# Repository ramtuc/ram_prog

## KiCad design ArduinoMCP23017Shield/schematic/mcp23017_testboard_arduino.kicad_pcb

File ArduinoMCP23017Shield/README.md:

# Arduino MCP23017 Shield

MCP23017 I2C GPIOエキスパンダーを使用したArduino UNO用シールド基板プロジェクトです。I2C通信で16個のGPIOピンを追加し、デジタル入出力を拡張できます。

## 特徴

- **16ピンのGPIO拡張**: MCP23017により16個のデジタルI/Oピンを追加
- **I2C通信**: わずか2本の信号線(SDA/SCL)で制御
- **柔軟な入出力設定**: 各ピンを独立して入力/出力に設定可能
- **アドレス選択可能**: 最大8個のMCP23017を接続可能(アドレス0x20-0x27)
- **2種類のサンプルプログラム**:
  - 出力テスト（シーケンシャルLED点灯）
  - 入出力テスト（入力→出力ループバック）

## ハードウェア

### 回路図

`schematic/` フォルダにKiCadプロジェクトファイルが含まれています：

- `mcp23017_testboard_arduino.kicad_sch` - 回路図
- `mcp23017_testboard_arduino.kicad_pcb` - PCBレイアウト
- `mcp23017_testboard_arduino.pdf` - 回路図PDF
- `bom .xls` - 部品表（BOM）
- `CPL.xlsx` - 部品配置リスト

### MCP23017について

MCP23017は、I2Cインターフェースで制御できる16ビットGPIOエキスパンダーです。

**主な仕様:**
- 16個の双方向I/Oピン（2つの8ビットポート: GPIOA, GPIOB）
- I2C通信（400kHzまで対応）
- 各ピンに内部プルアップ抵抗搭載
- 割り込み機能搭載
- 動作電圧: 1.8V～5.5V

**ピン配置:**
- **GPIOA (PA0-PA7)**: ポートA（ピン0-7）
- **GPIOB (PB0-PB7)**: ポートB（ピン8-15）

### 対応ボード

- Arduino UNO R3
- Arduino UNO R4 Minima
- Arduino UNO R4 WiFi
- ESP32（I2C対応ボード）

## サンプルプログラム

### 1. Arduino_mcp23017_testboard
MCP23017の出力機能テスト - 16ピンをシーケンシャルに点灯

**機能:**
- 16個の出力ピン（PA0-PA7, PB0-PB7）を順番にHIGH/LOW制御
- 各ピンを順次点灯してLEDテストが可能
- 200msごとに次のピンへ移動

**用途:**
- MCP23017の動作確認
- 16個のLED順次点灯
- 出力ポートの配線チェック

**コード例:**
```cpp
#include <Wire.h>
#include <Adafruit_MCP23X17.h>

Adafruit_MCP23X17 mcp;

void setup() {
  Wire.begin();
  mcp.begin_I2C();  // アドレス0x20
  
  // 全16ピンを出力に設定
  for (int i = 0; i < 16; i++) {
    mcp.pinMode(i, OUTPUT);
  }
}

void loop() {
  // 各ピンを順番に点灯
  for (int i = 0; i < 16; i++) {
    mcp.digitalWrite(i, HIGH);
    // 他のピンをLOWに
    for (int j = 0; j < 16; j++) {
      if (j != i) mcp.digitalWrite(j, LOW);
    }
    delay(200);
  }
}
```

### 2. Arduino_mcp23017_testboard_inout
MCP23017の入出力機能テスト - 入力読み取りと出力制御

**機能:**
- **ポートA (PA0-PA7)**: 出力ポート
- **ポートB (PB0-PB7)**: 入力ポート
- ポートBの入力状態をリアルタイムでポートAに反映
- Arduinoのデジタルピン0-7をランダムに制御

**用途:**
- 入力機能の動作確認
- スイッチ入力とLED出力の連動テスト
- ループバックテスト

**コード例:**
```cpp
void setup() {
  Wire.begin();
  mcp.begin_I2C();
  
  // ポートA (PA0-PA7): 出力
  for (int i = 0; i < 8; i++) {
    mcp.pinMode(i, OUTPUT);
  }
  
  // ポートB (PB0-PB7): 入力
  for (int i = 8; i < 16; i++) {
    mcp.pinMode(i, INPUT);
  }
}

void loop() {
  // ポートBの入力をポートAに反映
  for (int i = 0; i < 8; i++) {
    int state = mcp.digitalRead(i + 8);  // PB読み取り
    mcp.digitalWrite(i, state);          // PAに出力
  }
  delay(500);
}
```

## セットアップ

### 1. 必要なライブラリ

Arduino IDEのライブラリマネージャーからインストール：

- **Adafruit MCP23017 Library** (by Adafruit)
- **Wire** (Arduino標準ライブラリ)

```
スケッチ → ライブラリをインクルード → ライブラリを管理
「Adafruit MCP23017」で検索してインストール
```

### 2. ハードウェア接続

**I2C接続:**
- SDA → Arduino A4 (UNO) / GPIO21 (ESP32)
- SCL → Arduino A5 (UNO) / GPIO22 (ESP32)
- VDD → 5V (Arduino) / 3.3V (ESP32)
- GND → GND

**アドレス設定:**
- A0, A1, A2ピンでI2Cアドレスを設定
- デフォルト: 0x20 (A0=A1=A2=GND)

### 3. スケッチのアップロード

```bash
# Arduino IDEでスケッチを開く
Arduino_Schetch/Arduino_mcp23017_testboard/Arduino_mcp23017_testboard.ino
# または
Arduino_Schetch/Arduino_mcp23017_testboard_inout/Arduino_mcp23017_testboard_inout.ino

# ボードを選択: Arduino UNO R3/R4
# ポートを選択
# アップロード
```

## I2Cアドレス設定

MCP23017のI2Cアドレスは、A0、A1、A2ピンで設定します：

| A2 | A1 | A0 | アドレス |
|----|----|----|----------|
| 0  | 0  | 0  | 0x20     |
| 0  | 0  | 1  | 0x21     |
| 0  | 1  | 0  | 0x22     |
| 0  | 1  | 1  | 0x23     |
| 1  | 0  | 0  | 0x24     |
| 1  | 0  | 1  | 0x25     |
| 1  | 1  | 0  | 0x26     |
| 1  | 1  | 1  | 0x27     |

```cpp
// カスタムアドレスで初期化
mcp.begin_I2C(0x21);  // A0=HIGH, A1=A2=LOW
```

## 応用例

### 複数のMCP23017を使用

```cpp
Adafruit_MCP23X17 mcp1;
Adafruit_MCP23X17 mcp2;

void setup() {
  Wire.begin();
  mcp1.begin_I2C(0x20);  // 1つ目
  mcp2.begin_I2C(0x21);  // 2つ目
  
  // 合計32ピンの拡張が可能
}
```

### プルアップ抵抗の有効化

```cpp
// 内部プルアップを有効化（スイッチ入力に便利）
mcp.pinMode(0, INPUT_PULLUP);
```

### 割り込み機能の使用

```cpp
// ピン変化時に割り込みを発生
mcp.setupInterruptPin(0, CHANGE);
```

## トラブルシューティング

### I2Cデバイスが見つからない

1. 配線を確認（SDA/SCL、電源、GND）
2. I2Cスキャナーでアドレスを確認
3. プルアップ抵抗（4.7kΩ）がSDA/SCLに接続されているか確認

```cpp
// I2Cスキャナーコード
Wire.begin();
for (byte address = 1; address < 127; address++) {
  Wire.beginTransmission(address);
  if (Wire.endTransmission() == 0) {
    Serial.print("Found device at 0x");
    Serial.println(address, HEX);
  }
}
```

### ESP32で使用する場合

ESP32では、I2Cピンを明示的に指定する必要があります：

```cpp
Wire.begin(21, 22); // SDA=GPIO21, SCL=GPIO22
mcp.begin_I2C();
```

## 製造データ

### Gerberファイル

`schematic/` フォルダにPCB製造用のGerberファイルが含まれています：

- `mcp23017_testboard_arduino-F_Cu.gbr` - 表面銅箔
- `mcp23017_testboard_arduino-B_Cu.gbr` - 裏面銅箔
- `mcp23017_testboard_arduino-F_Mask.gbr` - 表面レジスト
- `mcp23017_testboard_arduino-B_Mask.gbr` - 裏面レジスト
- `mcp23017_testboard_arduino.drl` - ドリルデータ

### 部品表

詳細な部品リストは `schematic/bom .xls` を参照してください。

**主要部品:**
- MCP23017-E/SP (DIP-28)
- 抵抗、コンデンサ
- LEDインジケーター（オプション）

## 技術仕様

**MCP23017:**
- I2C通信速度: 100kHz (標準), 400kHz (Fast), 1.7MHz (High Speed)
- 出力電流: 最大25mA per pin
- 入力電圧: VDD+0.6V以内
- 動作温度: -40°C～+85°C

**基板サイズ:**
- Arduino UNO互換シールドフォームファクタ

## 参考資料

### 解説記事

- [ArduinoでMCP23017を使う - I2C GPIO拡張の基本](https://electwork.net/posts/arduino-mcp23017/)
- [ESP32でMCP23017を使う - I2C GPIO拡張の実践](https://electwork.net/posts/esp32-mcp23017/)

### 技術資料

- [MCP23017 データシート (Microchip)](https://www.microchip.com/en-us/product/MCP23017)
- [Adafruit MCP23017 Library Documentation](https://github.com/adafruit/Adafruit-MCP23017-Arduino-Library)
- [I2C通信の基礎](https://www.arduino.cc/en/Reference/Wire)

## ライセンス

MITライセンス

## 開発環境

- Arduino IDE 2.x
- KiCad 7.x
- Adafruit MCP23017 Library
- Arduino UNO R3/R4 / ESP32

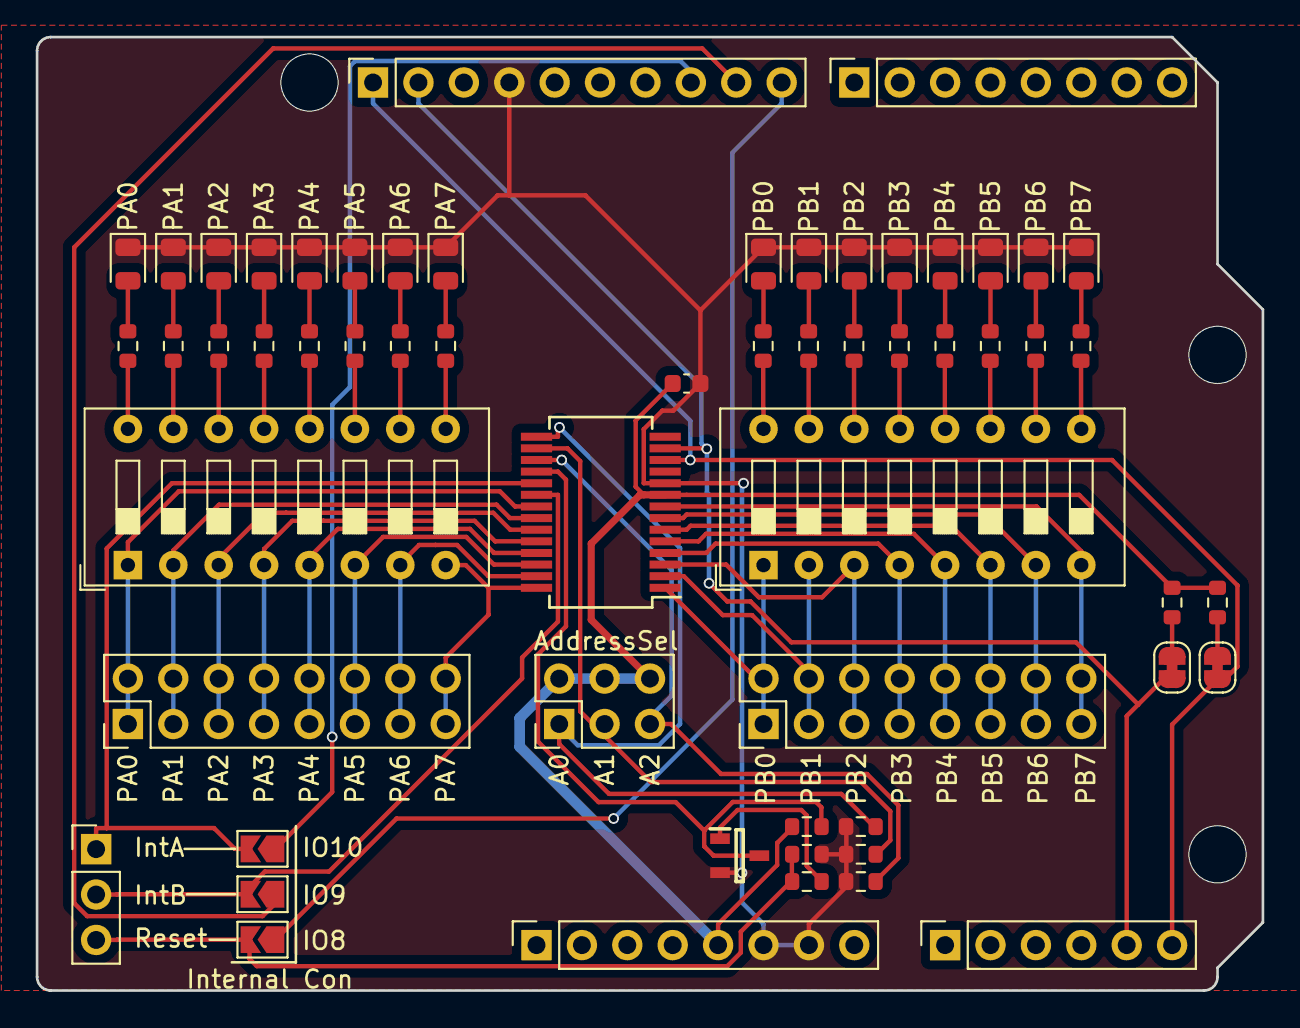
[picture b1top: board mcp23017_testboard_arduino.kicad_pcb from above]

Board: 2 copper layers, 68.6 x 53.3 mm, 61 parts (0 on the bottom side), 65 nets.

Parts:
C1: 0.1u; C_0603_1608Metric
D1, D2, D3, D4, D5, D6, D7, D8, D9, D10, D11, D12, D13, D14, D15, D16: green; LED_0805_2012Metric
J1: Power; PinSocket_1x08_P2.54mm_Vertical
J2: Digital/PWM; PinSocket_1x10_P2.54mm_Vertical
J3: Analog; PinSocket_1x06_P2.54mm_Vertical
J4: Digital/PWM; PinSocket_1x08_P2.54mm_Vertical
J5: Conn_01x06_Pin; PinHeader_2x03_P2.54mm_Vertical
J6, J7: Conn_01x16_Pin; PinHeader_2x08_P2.54mm_Vertical
J8: Conn_01x03_Pin; PinHeader_1x03_P2.54mm_Vertical
JP1: SDA; SolderJumper-2_P1.3mm_Bridged_RoundedPad1.0x1.5mm
JP2: SCL; SolderJumper-2_P1.3mm_Bridged_RoundedPad1.0x1.5mm
JP6: INTA; SolderJumper-2_P1.3mm_Open_TrianglePad1.0x1.5mm
JP7: INTB; SolderJumper-2_P1.3mm_Open_TrianglePad1.0x1.5mm
JP8: RST; SolderJumper-2_P1.3mm_Open_TrianglePad1.0x1.5mm
MH1, MH3, MH4: MountingHole_3.2mm
Q1: SS8050-G; SOT95P240X115-3N
R1, R2, R3, R4, R5: 3.3k; R_0603_1608Metric
R6, R7, R8, R9, R10, R11, R12, R13, R14, R15, R16, R17, R18, R19, R20, R21: 330; R_0603_1608Metric
R22: 10k; R_0603_1608Metric
R23: 47k; R_0603_1608Metric
R24: 4.7k; R_0603_1608Metric
SW1, SW2: SW_DIP_x08; SW_DIP_SPSTx08_Slide_9.78x22.5mm_W7.62mm_P2.54mm
U1: MCP23017_SS; SSOP-28_5.3x10.2mm_P0.65mm

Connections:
+5V: C1.2, J1.5, J5.2, J5.4, J5.6, R1.1, R2.1, R22.1, U1.9 (VDD)
/8: J2.10, JP8.1 (A)
/*9: J2.9, JP7.1 (A)
/*10: J2.8, JP6.1 (A)
/EX_RESET: J8.3, JP8.2 (B), R23.1, R24.1
/INTA: J8.1, JP6.2 (B), U1.19 (INTB)
/INTB: J8.2, JP7.2 (B), U1.20 (INTA)
/RESET: Q1.3, R22.2, U1.18 (~RESET)
/SCL: J2.1, J3.6, JP2.2 (B), U1.12 (SCK)
/SDA: J2.2, J3.5, JP1.2 (B), U1.13 (SDA)
GND: C1.1, D1.1 (K), D2.1 (K), D3.1 (K), D4.1 (K), D5.1 (K), D6.1 (K), D7.1 (K), D8.1 (K), D9.1 (K), D10.1 (K), D11.1 (K), D12.1 (K), D13.1 (K), D14.1 (K), D15.1 (K), D16.1 (K), J1.6, J1.7, J2.4, Q1.2, R3.1, R4.1, R5.1, R23.2, U1.10 (VSS)
unnamed: D1.2 (A), R6.2
unnamed: D2.2 (A), R7.2
unnamed: D3.2 (A), R8.2
unnamed: D4.2 (A), R9.2
unnamed: D5.2 (A), R10.2
unnamed: D6.2 (A), R11.2
unnamed: D7.2 (A), R12.2
unnamed: D8.2 (A), R13.2
unnamed: D9.2 (A), R14.2
unnamed: D10.2 (A), R15.2
unnamed: D11.2 (A), R16.2
unnamed: D12.2 (A), R17.2
unnamed: D13.2 (A), R18.2
unnamed: D14.2 (A), R19.2
unnamed: D15.2 (A), R20.2
unnamed: D16.2 (A), R21.2
unnamed: J5.1, R3.2, U1.15 (A0)
unnamed: J5.3, R4.2, U1.16 (A1)
unnamed: J5.5, R5.2, U1.17 (A2)
unnamed: J6.1, J6.2, SW1.1, U1.1 (GPB0)
unnamed: J6.3, J6.4, SW1.2, U1.2 (GPB1)
unnamed: J6.5, J6.6, SW1.3, U1.3 (GPB2)
unnamed: J6.7, J6.8, SW1.4, U1.4 (GPB3)
unnamed: J6.9, J6.10, SW1.5, U1.5 (GPB4)
unnamed: J6.11, J6.12, SW1.6, U1.6 (GPB5)
unnamed: J6.13, J6.14, SW1.7, U1.7 (GPB6)
unnamed: J6.15, J6.16, SW1.8, U1.8 (GPB7)
unnamed: J7.1, J7.2, SW2.1, U1.21 (GPA0)
unnamed: J7.3, J7.4, SW2.2, U1.22 (GPA1)
unnamed: J7.5, J7.6, SW2.3, U1.23 (GPA2)
unnamed: J7.7, J7.8, SW2.4, U1.24 (GPA3)
unnamed: J7.9, J7.10, SW2.5, U1.25 (GPA4)
unnamed: J7.11, J7.12, SW2.6, U1.26 (GPA5)
unnamed: J7.13, J7.14, SW2.7, U1.27 (GPA6)
unnamed: J7.15, J7.16, SW2.8, U1.28 (GPA7)
unnamed: JP1.1 (A), R1.2
unnamed: JP2.1 (A), R2.2
unnamed: Q1.1, R24.2
unnamed: R6.1, SW1.16
unnamed: R7.1, SW1.15
unnamed: R8.1, SW1.14
unnamed: R9.1, SW1.13
unnamed: R10.1, SW1.12
unnamed: R11.1, SW1.11
unnamed: R12.1, SW1.10
unnamed: R13.1, SW1.9
unnamed: R14.1, SW2.16
unnamed: R15.1, SW2.15
unnamed: R16.1, SW2.14
unnamed: R17.1, SW2.13
unnamed: R18.1, SW2.12
unnamed: R19.1, SW2.11
unnamed: R20.1, SW2.10
unnamed: R21.1, SW2.9

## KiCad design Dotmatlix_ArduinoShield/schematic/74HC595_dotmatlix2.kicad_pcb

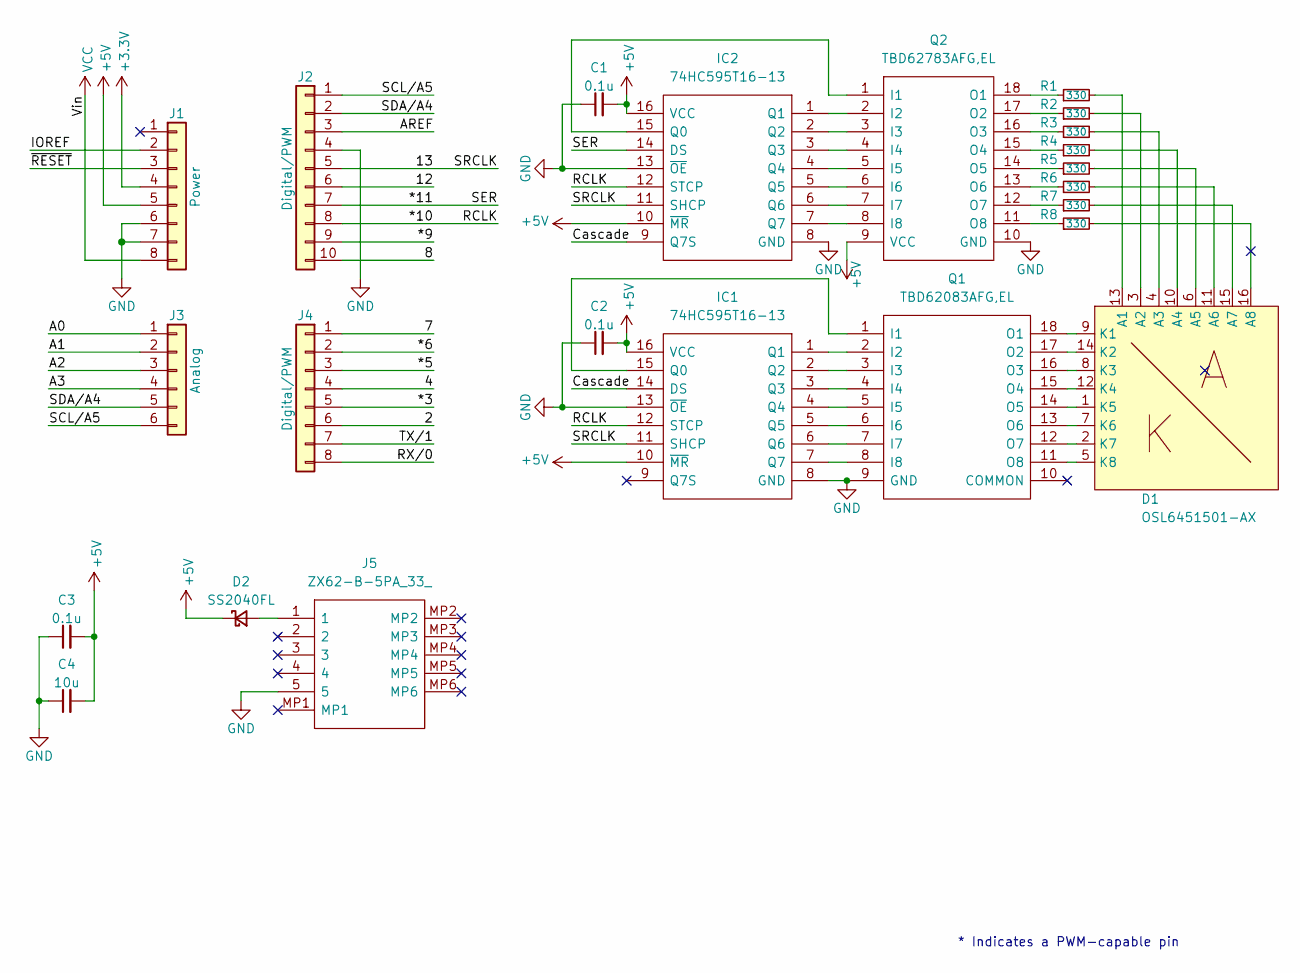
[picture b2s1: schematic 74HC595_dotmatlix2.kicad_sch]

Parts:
C1, C2, C3: 0.1u; C_0603_1608Metric
C4: 10u; C_0805_2012Metric
D1: OSL6451501-AX; OSL641501-AX
D2: SS2040FL; D_SOD-123F
IC1, IC2: 74HC595T16-13; SOP65P640X108-16N; Mouser Part Number 621-74HC595T16-13
J1: Power; PinSocket_1x08_P2.54mm_Vertical
J2: Digital/PWM; PinSocket_1x10_P2.54mm_Vertical
J3: Analog; PinSocket_1x06_P2.54mm_Vertical
J4: Digital/PWM; PinSocket_1x08_P2.54mm_Vertical
J5: ZX62-B-5PA_33_; ZX62B5PA33; Mouser Part Number 798-ZX62-B-5PA33
Q1: TBD62083AFG,EL; SOIC127P1030X245-18N; Mouser Part Number 757-TBD62083AFGEL
Q2: TBD62783AFG,EL; SOIC127P1030X245-18N; Mouser Part Number 757-TBD62783AFGEL
R1, R2, R3, R4, R5, R6, R7, R8: 330; R_0603_1608Metric

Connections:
+3V3: J1.4
+5V: C1.2, C2.2, C3.2, C4.2, D2.1 (K), IC1.10 (~MR), IC1.16 (VCC), IC2.10 (~MR), IC2.16 (VCC), J1.5, Q2.9 (VCC)
/2: J4.6
/4: J4.4
/7: J4.1
/8: J2.10
/12: J2.6
/13: IC1.11 (SHCP), IC2.11 (SHCP), J2.5
/*3: J4.5
/*5: J4.3
/*6: J4.2
/*9: J2.9
/*10: IC1.12 (STCP), IC2.12 (STCP), J2.8
/*11: IC2.14 (DS), J2.7
/A0: J3.1
/A1: J3.2
/A2: J3.3
/A3: J3.4
/AREF: J2.3
/Cascade: IC1.14 (DS), IC2.9 (Q7S)
/IOREF: J1.2
/RX/0: J4.8
/SCL/A5: J2.1, J3.6
/SDA/A4: J2.2, J3.5
/TX/1: J4.7
/~RESET: J1.3
GND: C1.1, C2.1, C3.1, C4.1, IC1.8 (GND), IC1.13 (~OE), IC2.8 (GND), IC2.13 (~OE), J1.6, J1.7, J2.4, J5.5, Q1.9 (GND), Q2.10 (GND)
unnamed: D1.13 (A1), R1.2
unnamed: D1.3 (A2), R2.2
unnamed: D1.4 (A3), R3.2
unnamed: D1.10 (A4), R4.2
unnamed: D1.6 (A5), R5.2
unnamed: D1.11 (A6), R6.2
unnamed: D1.15 (A7), R7.2
unnamed: D1.16 (A8), R8.2
unnamed: D1.9 (K1), Q1.18 (O1)
unnamed: D1.14 (K2), Q1.17 (O2)
unnamed: D1.8 (K3), Q1.16 (O3)
unnamed: D1.12 (K4), Q1.15 (O4)
unnamed: D1.1 (K5), Q1.14 (O5)
unnamed: D1.7 (K6), Q1.13 (O6)
unnamed: D1.2 (K7), Q1.12 (O7)
unnamed: D1.5 (K8), Q1.11 (O8)
unnamed: D2.2 (A), J5.1
unnamed: IC1.15 (Q0), Q1.1 (I1)
unnamed: IC1.1 (Q1), Q1.2 (I2)
unnamed: IC1.2 (Q2), Q1.3 (I3)
unnamed: IC1.3 (Q3), Q1.4 (I4)
unnamed: IC1.4 (Q4), Q1.5 (I5)
unnamed: IC1.5 (Q5), Q1.6 (I6)
unnamed: IC1.6 (Q6), Q1.7 (I7)
unnamed: IC1.7 (Q7), Q1.8 (I8)
unnamed: IC2.15 (Q0), Q2.1 (I1)
unnamed: IC2.1 (Q1), Q2.2 (I2)
unnamed: IC2.2 (Q2), Q2.3 (I3)
unnamed: IC2.3 (Q3), Q2.4 (I4)
unnamed: IC2.4 (Q4), Q2.5 (I5)
unnamed: IC2.5 (Q5), Q2.6 (I6)
unnamed: IC2.6 (Q6), Q2.7 (I7)
unnamed: IC2.7 (Q7), Q2.8 (I8)
unnamed: Q2.18 (O1), R1.1
unnamed: Q2.17 (O2), R2.1
unnamed: Q2.16 (O3), R3.1
unnamed: Q2.15 (O4), R4.1
unnamed: Q2.14 (O5), R5.1
unnamed: Q2.13 (O6), R6.1
unnamed: Q2.12 (O7), R7.1
unnamed: Q2.11 (O8), R8.1
VCC: J1.8

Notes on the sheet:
* Indicates a PWM-capable pin

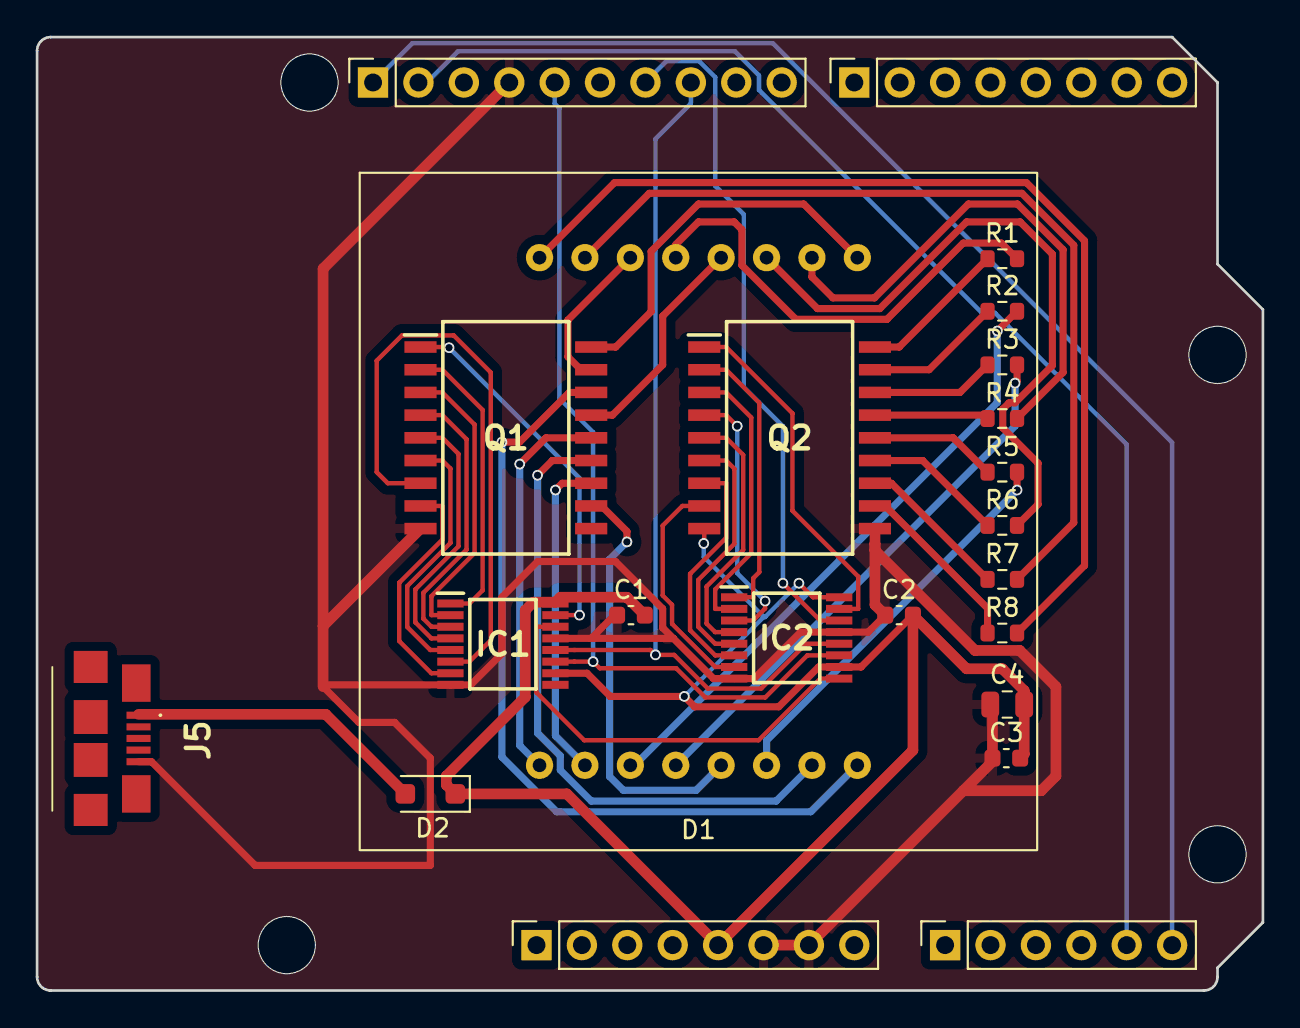
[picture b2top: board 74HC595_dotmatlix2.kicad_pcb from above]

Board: 2 copper layers, 68.6 x 53.3 mm, 27 parts (0 on the bottom side), 49 nets.

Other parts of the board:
MH1, MH2, MH3, MH4: MountingHole_3.2mm

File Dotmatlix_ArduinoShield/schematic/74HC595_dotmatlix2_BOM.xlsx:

Comment | Designator | Footprint | JLCPCB Part #（optional）
0.1u | C1,C2,C3 | C_0603_1608Metric
10u | C4 | C_0805_2012Metric
SS2040FL | D2 | D_SOD-123F
74HC595T16-13 | IC1,IC2 | SOP65P640X108-16N
ZX62-B-5PA_33_ | J5 | ZX62B5PA33
TBD62083AFG,EL | Q1 | SOIC127P1030X245-18N
TBD62783AFG,EL | Q2 | SOIC127P1030X245-18N
330 | R1,R2,R3,R4,R5,R6,R7,R8 | R_0603_1608Metric

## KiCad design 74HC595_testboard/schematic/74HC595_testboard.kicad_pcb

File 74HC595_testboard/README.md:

# 74HC595 LED Test Board

74HC595シフトレジスタを5個カスケード接続して40個のLEDを制御するArduino用テストボードプロジェクトです。わずか3本の信号線で大量のLEDを制御できます。

## 特徴

- **40個のLED制御**: 74HC595を5個カスケード接続
- **3本の信号線のみ**: DATA、CLOCK、LATCHの3本で制御
- **2種類の制御方法**:
  - GPIO制御（shiftOut関数）
  - SPI通信（高速転送）
- **多彩なアニメーションパターン**: ウェーブ、チェイス、ランダムなど
- **拡張性**: さらに74HC595を追加して無限に拡張可能

## ハードウェア

### 回路図

`schematic/` フォルダにKiCadプロジェクトファイルが含まれています：

- `74HC595_testboard.kicad_sch` - 回路図
- `74HC595_testboard.kicad_pcb` - PCBレイアウト
- `74HC595_testboard.pdf` - 回路図PDF
- `74HC595_testboardBOM_JLCSMT.xlsx` - 部品表（BOM）
- `74HC595_testboard_CPL1.xlsx` - 部品配置リスト
- `74HC595_testboard.zip` - Gerberファイル一式

### 74HC595について

74HC595は、シリアル入力をパラレル出力に変換する8ビットシフトレジスタです。

**主な仕様:**
- 8ビットのパラレル出力
- カスケード接続可能（Q7'ピンで次段へデータ転送）
- 3線式制御（SER、SRCLK、RCLK）
- 出力電流: 最大35mA per pin
- 動作電圧: 2V～6V
- 高速動作: 最大100MHz（5V時）

**ピン説明:**
- **SER (DS)**: シリアルデータ入力
- **SRCLK (SHCP)**: シフトレジスタクロック
- **RCLK (STCP)**: ストレージレジスタクロック（ラッチ）
- **Q0-Q7**: パラレル出力
- **Q7'**: 次段へのシリアル出力（カスケード接続用）
- **OE**: 出力イネーブル（通常はGNDに接続）
- **SRCLR**: クリア（通常はVCCに接続）

### カスケード接続

5個の74HC595を数珠つなぎに接続することで、40個の独立した出力を制御：

```
Arduino → [74HC595 #1] → [74HC595 #2] → [74HC595 #3] → [74HC595 #4] → [74HC595 #5]
  (3pin)       ↓              ↓              ↓              ↓              ↓
             Q0-Q7         Q8-Q15        Q16-Q23        Q24-Q31        Q32-Q39
```

### 対応ボード

- Arduino UNO R3
- Arduino UNO R4 Minima
- Arduino UNO R4 WiFi
- その他のArduino互換ボード

## サンプルプログラム

### 1. 74HC595_test
GPIOピンでの制御（shiftOut関数を使用）

**ピン接続:**
- データピン (SER): D2
- ラッチピン (RCLK): D3
- クロックピン (SRCLK): D4

**アニメーションパターン:**

1. **ウェーブパターン** - 1つのLEDが端から端まで移動
2. **ダブルチェイスパターン** - 2つのLEDが追いかけっこ
3. **中央から放射パターン** - 中央から両端へ展開
4. **チャーサーパターン** - 4つのLEDが連なって移動
5. **プログレスバー** - LEDが順次点灯してバーが伸びる
6. **ランダムパターン** - LEDがランダムに点滅

**コード構造:**
```cpp
const int dataPin = 2;     // SERピン
const int latchPin = 3;    // RCLKピン
const int clockPin = 4;    // SRCLKピン

void updateShiftRegisters(uint64_t data) {
  digitalWrite(latchPin, LOW);
  // 5バイト分のデータを送信（MSBから）
  for (int i = 4; i >= 0; i--) {
    shiftOut(dataPin, clockPin, MSBFIRST, (data >> (8 * i)) & 0xFF);
  }
  digitalWrite(latchPin, HIGH);
}
```

**主要パターン関数:**
```cpp
// ウェーブ: 単一LEDが順次移動
void wavePattern() {
  for (int j = 0; j < 40; j++) {
    uint64_t pattern = 1ULL << j;
    updateShiftRegisters(pattern);
    delay(100);
  }
}

// 中央から放射
void middleOutPattern() {
  int middle = 20;
  for (int j = 0; j <= middle; j++) {
    uint64_t pattern = (1ULL << (middle - j)) | (1ULL << (middle + j));
    updateShiftRegisters(pattern);
    delay(100);
  }
}

// ランダム点灯
void randomPattern() {
  for (int j = 0; j < 40; j++) {
    uint64_t pattern = random(0x10000000000ULL);
    updateShiftRegisters(pattern);
    delay(100);
  }
}
```

### 2. 74HC595_SPI_test
SPI通信での制御（高速転送）

**ピン接続（SPI標準ピン）:**
- データピン (MOSI): D11
- ラッチピン (SS): D10
- クロックピン (SCK): D13

**特徴:**
- SPI.transfer()を使用した高速データ転送
- シンプルなシーケンシャル点灯
- 転送速度が向上（最大8MHz）

**コード:**
```cpp
#include <SPI.h>

const int latchPin = 10;

void setup() {
  SPI.begin();
  pinMode(latchPin, OUTPUT);
}

void loop() {
  for (int i = 0; i < 40; i++) {
    digitalWrite(latchPin, LOW);
    
    // 5個の74HC595にデータ送信
    for (int j = 4; j >= 0; j--) {
      if (i/8 == j) {
        SPI.transfer(1 << (i % 8));  // 該当するICにビットを送信
      } else {
        SPI.transfer(0);             // 他のICは0
      }
    }
    
    digitalWrite(latchPin, HIGH);
    delay(20);
  }
}
```

## セットアップ

### 1. ハードウェアの準備

1. PCBを製造（Gerberファイルを使用）
2. 部品表（BOM）を参照して部品を実装
3. Arduinoに接続

### 2. スケッチのアップロード

**GPIO制御版:**
```bash
Arduino_Schetch/74HC595_test/74HC595_test.ino
```

**SPI制御版:**
```bash
Arduino_Schetch/74HC595_SPI_test/74HC595_SPI_test.ino
```

Arduino IDEで開いて、ボードとポートを選択してアップロードします。

## 技術的詳細

### データ転送の仕組み

74HC595は2段階でデータを転送します：

1. **シフト段階（SRCLK）**: 
   - SRCLKの立ち上がりエッジでSERピンのデータを取り込み
   - データは内部シフトレジスタにシフトされる
   - 8ビット分シフトすると、次の74HC595へQ7'から出力

2. **ラッチ段階（RCLK）**:
   - RCLKの立ち上がりエッジでシフトレジスタの内容を出力レジスタへコピー
   - 出力ピン（Q0-Q7）に反映される

```cpp
digitalWrite(latchPin, LOW);    // ラッチを無効化
shiftOut(dataPin, clockPin, MSBFIRST, data); // データ転送
digitalWrite(latchPin, HIGH);   // ラッチを有効化→出力に反映
```

### 40ビットデータの扱い

Arduinoの`uint64_t`型（64ビット）を使用して40ビット分のLEDパターンを表現：

```cpp
uint64_t pattern = 0x0000000001; // LED 0のみ点灯
uint64_t pattern = 0xFFFFFFFFFF; // 全40個のLED点灯
uint64_t pattern = 1ULL << 20;   // LED 20のみ点灯
```

### shiftOut vs SPI

| 方式 | 速度 | 柔軟性 | 使用ピン |
|------|------|--------|----------|
| shiftOut | 遅い | 任意のピン使用可能 | 任意の3ピン |
| SPI | 高速（最大8MHz） | 固定ピンのみ | D10, D11, D13 |

**速度比較:**
- shiftOut: 約5kHz
- SPI: 最大8MHz（約1600倍高速）

## カスタマイズ

### アニメーション速度の調整

```cpp
delay(100);  // この値を変更して速度調整
```

### 新しいパターンの追加

```cpp
void myCustomPattern() {
  // 独自のパターンを実装
  uint64_t pattern = 0x5555555555ULL; // 交互パターン
  updateShiftRegisters(pattern);
}
```

### さらに74HC595を追加

74HC595を追加する場合は、データ型を変更：

```cpp
// 6個（48ビット）の場合
uint64_t data; // 64ビットでOK

// 9個以上（72ビット以上）の場合
// 配列やバイト配列を使用
byte data[10]; // 10バイト = 80ビット
```

## 応用例

### PWM制御でLED輝度調整

```cpp
// ソフトウェアPWMで輝度制御
void dimPattern(uint64_t pattern, int brightness) {
  for (int i = 0; i < 100; i++) {
    updateShiftRegisters(pattern);
    delayMicroseconds(brightness * 10);
    updateShiftRegisters(0);
    delayMicroseconds((100 - brightness) * 10);
  }
}
```

### マルチプレクス表示

複数のパターンを高速切り替えで表示：

```cpp
uint64_t frames[10]; // 10フレーム分
void displayFrames() {
  for (int i = 0; i < 10; i++) {
    updateShiftRegisters(frames[i]);
    delay(50); // フレームレート: 20fps
  }
}
```

## トラブルシューティング

### LEDが点灯しない

1. 電源電圧を確認（74HC595: 2-6V）
2. 配線を確認（SER、SRCLK、RCLK）
3. OEピンがGNDに接続されているか確認
4. SRCLRピンがVCCに接続されているか確認

### 一部のLEDが点灯しない

1. カスケード接続の配線を確認
2. 各74HC595の電源を確認
3. LED用の電流制限抵抗値を確認

### データが正しく転送されない

1. クロック周波数を下げる（delay追加）
2. GNDがArduinoと74HC595で共通か確認
3. 配線の長さを短くする（ノイズ対策）

## 製造データ

### Gerberファイル

`schematic/74HC595_testboard.zip` に製造用ファイルが含まれています。

### 部品表

詳細は `schematic/74HC595_testboardBOM_JLCSMT.xlsx` を参照してください。

**主要部品:**
- 74HC595 x5
- LED x40
- 抵抗（LED用電流制限）
- コンデンサ（デカップリング）

## 技術仕様

**74HC595:**
- 出力電流: 最大35mA per pin (70mA合計推奨)
- クロック周波数: 最大100MHz（5V時）
- 伝搬遅延: 14ns typ（5V時）
- 動作電圧: 2V～6V
- 動作温度: -40°C～+85°C

**消費電力:**
- 全LED点灯時: 約800mA（LED 40個 x 20mA）
- 74HC595 x5: 約10mA

## 参考資料

### 解説記事

- [74HC595シフトレジスタでLEDボード製作 - 40個のLED制御方法](https://electwork.net/posts/arduino-74hc595-led-board/)

### 技術資料

- [74HC595 データシート (Texas Instruments)](https://www.ti.com/product/SN74HC595)
- [Arduino shiftOut() Reference](https://www.arduino.cc/reference/en/language/functions/advanced-io/shiftout/)
- [Arduino SPI Library](https://www.arduino.cc/en/reference/SPI)
- [シフトレジスタの基礎](https://learn.sparkfun.com/tutorials/shift-registers)

## ライセンス

MITライセンス

## 開発環境

- Arduino IDE 2.x
- KiCad 7.x
- Arduino UNO R3/R4

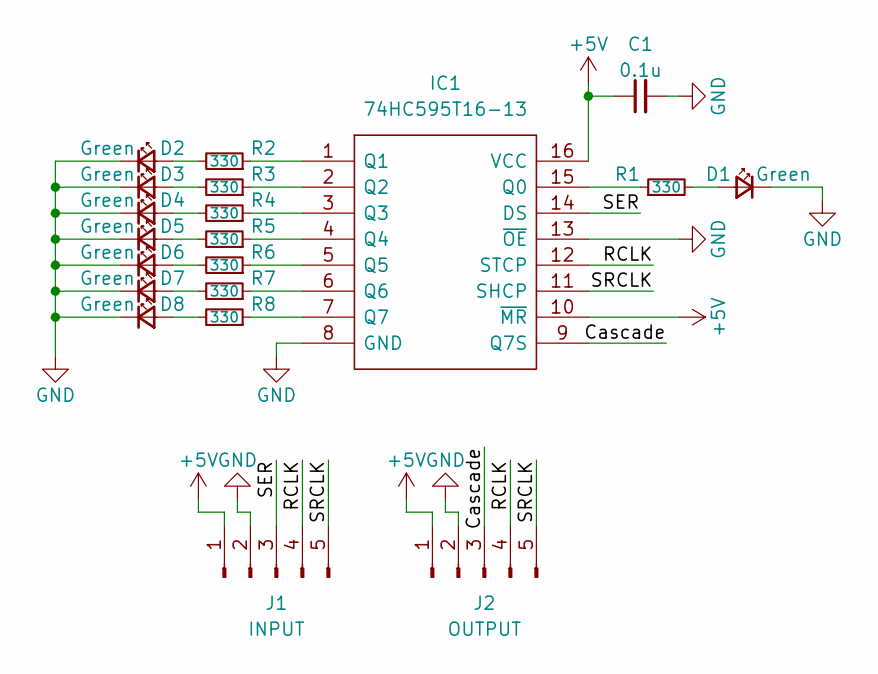
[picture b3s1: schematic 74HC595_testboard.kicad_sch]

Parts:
C1: 0.1u; C_0603_1608Metric_Pad1.08x0.95mm_HandSolder
D1, D2, D3, D4, D5, D6, D7, D8: Green; LED_0805_2012Metric_Pad1.15x1.40mm_HandSolder
IC1: 74HC595T16-13; SOP65P640X108-16N; Mouser Part Number 621-74HC595T16-13
J1: INPUT; PinHeader_1x05_P2.54mm_Vertical
J2: OUTPUT; PinHeader_1x05_P2.54mm_Vertical
R1, R2, R3, R4, R5, R6, R7, R8: 330; R_0603_1608Metric_Pad0.98x0.95mm_HandSolder

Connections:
+5V: C1.1, IC1.10 (~MR), IC1.16 (VCC), J1.1, J2.1
/Cascade: IC1.9 (Q7S), J2.3
/RCLK: IC1.12 (STCP), J1.4, J2.4
/SER: IC1.14 (DS), J1.3
/SRCLK: IC1.11 (SHCP), J1.5, J2.5
GND: C1.2, D1.1 (K), D2.1 (K), D3.1 (K), D4.1 (K), D5.1 (K), D6.1 (K), D7.1 (K), D8.1 (K), IC1.8 (GND), IC1.13 (~OE), J1.2, J2.2
unnamed: D1.2 (A), R1.2
unnamed: D2.2 (A), R2.2
unnamed: D3.2 (A), R3.2
unnamed: D4.2 (A), R4.2
unnamed: D5.2 (A), R5.2
unnamed: D6.2 (A), R6.2
unnamed: D7.2 (A), R7.2
unnamed: D8.2 (A), R8.2
unnamed: IC1.15 (Q0), R1.1
unnamed: IC1.1 (Q1), R2.1
unnamed: IC1.2 (Q2), R3.1
unnamed: IC1.3 (Q3), R4.1
unnamed: IC1.4 (Q4), R5.1
unnamed: IC1.5 (Q5), R6.1
unnamed: IC1.6 (Q6), R7.1
unnamed: IC1.7 (Q7), R8.1

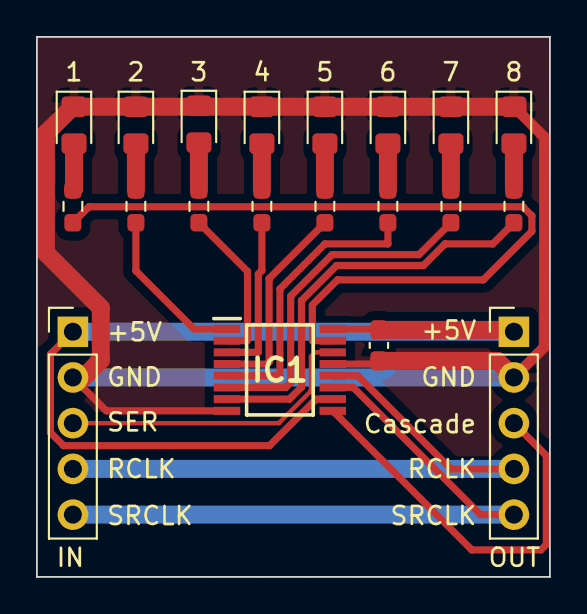
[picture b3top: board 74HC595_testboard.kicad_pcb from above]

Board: 2 copper layers, 28.5 x 30.0 mm, 20 parts (0 on the bottom side), 22 nets.

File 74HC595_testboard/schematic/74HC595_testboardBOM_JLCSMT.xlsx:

Comment | Designator | Footprint | JLCPCB Part #（optional）
LED Green | D1,D2,D3,D4,D5,D6,D7,D8 | LED_0805_2012Metric_Pad1.15x1.40mm_HandSolder
0.1u | C1 | C_0603_1608Metric_Pad1.08x0.95mm_HandSolder
330 | R1,R2,R3,R4,R5,R6,R7,R8 | R_0603_1608Metric_Pad0.98x0.95mm_HandSolder
74HC595T16-13 | IC1 | SOP65P640X108-16N

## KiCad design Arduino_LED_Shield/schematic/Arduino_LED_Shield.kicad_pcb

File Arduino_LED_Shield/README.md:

# Arduino LED Shield

Arduino UNO用の20個のLEDを制御するシールド基板プロジェクトです。デジタルピン(D0-D13)とアナログピン(A0-A5)をすべて使用してLEDアニメーションを実現します。

## 特徴

- **20個のLED制御**: デジタルピン14個 + アナログピン6個
- **ソフトウェアPWM**: 全ピンでPWM制御が可能
- **3種類のデモプログラム**:
  - LED動作テスト
  - 波形アニメーション
  - セルオートマトン

## ハードウェア

### 回路図

`schematic/` フォルダにKiCadプロジェクトファイルが含まれています：

- `Arduino_LED_Shield.kicad_sch` - 回路図
- `Arduino_LED_Shield.kicad_pcb` - PCBレイアウト
- `Arduino_LED_Shield.pdf` - 回路図PDF
- `bom.xls` - 部品表（BOM）
- `CPL.xlsx` - 部品配置リスト

### LED配置

- **D0-D13**: 14個のLED（波形表示用）
- **A0-A5**: 6個のLED（メーター/カウンター表示用）

### 対応ボード

- Arduino UNO R3
- Arduino UNO R4 Minima
- Arduino UNO R4 WiFi

## サンプルプログラム

### 1. LED_test
基本的な動作確認用プログラム

**機能:**
- 全LED一斉点滅
- シーケンシャル点灯（順次点灯）

**用途:**
- 基板の動作確認
- 各LEDの配線チェック

**詳細記事:**
- [Arduino全PINデバッグ - 20個のLEDで全ピン動作確認](https://electwork.net/posts/arduino-led-shield/)

```arduino
void loop() {
  for(int i = 0; i < 3; i++) {
    blinkAllLEDs();       // 全LED点滅
    sequentialBlink();    // 順次点灯
  }
}
```

### 2. LED_wave
3パターンのPWM波形アニメーション

**パターン（10秒ごとに自動切り替え）:**
1. **Deep Ocean** - ゆったりとした大きな波
2. **Cyber Pulse** - 高速で細かい逆方向の波
3. **Sonar Ripple** - 中心から外へ広がる波

**特徴:**
- ソフトウェアPWM実装
- ガンマ補正による滑らかな輝度変化
- A0-A5ピンでリアルタイムメーター表示

**詳細記事:**
- [ArduinoでソフトウェアPWM波形アニメーション - 3パターンのLEDエフェクト](https://electwork.net/posts/arduino-software-pwm-wave/)

```arduino
// パターンは10秒ごとに自動切り替え
int pattern = (millis() / 10000) % 3;
```

### 3. cellular-automaton
セルオートマトンによる生命的パターン生成

**ルール（自動切り替え）:**
- **Rule 30** - カオス的パターン
- **Rule 90** - フラクタル構造
- **Rule 110** - 複雑な振る舞い

**機能:**
- D0-D13: セルの状態表示
- A0-A5: 世代カウンターのバイナリ表示
- 64世代ごとにルール切り替え
- ルール切り替え時に5秒間の点滅演出

**詳細記事:**
- [Arduinoでセルオートマトン - Rule 30/90/110の視覚化](https://electwork.net/posts/arduino-cellular-automaton/)

```arduino
int rules[] = { 30, 90, 110 }; 
// 各ルールを64世代ずつ実行
```

## セットアップ

### 1. ハードウェアの準備

1. PCBを製造（Gerberファイルを使用）
2. 部品表（BOM）を参照して部品を実装
3. Arduino UNOに取り付け

### 2. ソフトウェアのアップロード

```bash
# Arduino IDEで任意のスケッチを開く
Arduino_Schetch/LED_test/LED_test.ino
Arduino_Schetch/LED_wave/LED_wave.ino
Arduino_Schetch/cellular-automaton/cellular-automaton.ino

# ボードを選択: Arduino UNO R3/R4
# ポートを選択
# アップロード
```

## 回路設計について

### KiCadプロジェクト

プロジェクトファイルは `schematic/` フォルダに配置されています。

**ファイル構成:**
- `.kicad_pro` - プロジェクト設定
- `.kicad_sch` - 回路図
- `.kicad_pcb` - PCBレイアウト
- `.kicad_prl` - プロジェクトローカル設定

### 製造データ

製造用のGerberファイルとドキュメント：
- `bom.xls` - 部品表
- `CPL.xlsx` - 部品配置リスト（SMD実装用）
- `Arduino_LED_Shield.pdf` - 回路図PDF
- `Arduino_LED_Shield.zip` - Gerberファイル一式

## 技術的詳細

### ソフトウェアPWM

Arduino UNOはハードウェアPWMピンが限られているため、全20ピンでソフトウェアPWMを実装しています。

```cpp
unsigned long pwmStart = micros();
while (micros() - pwmStart < 5000) { // 5ms PWMサイクル
  int pwmCycle = micros() & 0xFF; // 0-255
  digitalWrite(pin, (brightness > pwmCycle) ? HIGH : LOW);
}
```

### ガンマ補正

LEDの視覚的な輝度を改善するため、2乗カーブでガンマ補正を適用：

```cpp
int corrected = (brightness * brightness) / 255;
```

### セルオートマトンアルゴリズム

8通りの近傍パターンをルール番号のビット列で判定：

```cpp
int pattern = (left << 2) | (center << 1) | right; // 0-7
nextState = (ruleNumber >> pattern) & 1;
```

## カスタマイズ

### 速度調整

```cpp
delay(120);  // LED_waveやcellular-automatonの更新間隔
```

### パターン追加

新しい波形パターンやセルオートマトンのルールを追加可能：

```cpp
// LED_wave.inoに新しいパターンを追加
if (pattern == 3) {
  // 新しいアニメーション
}

// cellular-automaton.inoに新しいルールを追加
int rules[] = { 30, 90, 110, 184 }; // Rule 184を追加
```

## 必要な材料

- Arduino UNO R3/R4
- LED x20
- 抵抗（LED用）
- カスタムシールドPCB

詳細は `schematic/bom.xls` を参照してください。

## ライセンス

MITライセンス

## 参考資料

### 解説記事

- [Arduino全PINデバッグ - 20個のLEDで全ピン動作確認](https://electwork.net/posts/arduino-led-shield/)
- [ArduinoでソフトウェアPWM波形アニメーション](https://electwork.net/posts/arduino-software-pwm-wave/)
- [Arduinoでセルオートマトン - Rule 30/90/110の視覚化](https://electwork.net/posts/arduino-cellular-automaton/)

### 技術資料

- [セルオートマトン - Wikipedia](https://ja.wikipedia.org/wiki/セルオートマトン)
- [Elementary Cellular Automaton](http://mathworld.wolfram.com/ElementaryCellularAutomaton.html)
- [Arduino Software PWM](https://docs.arduino.cc/)

## 開発環境

- Arduino IDE 2.x
- KiCad 7.x
- Arduino UNO R3/R4

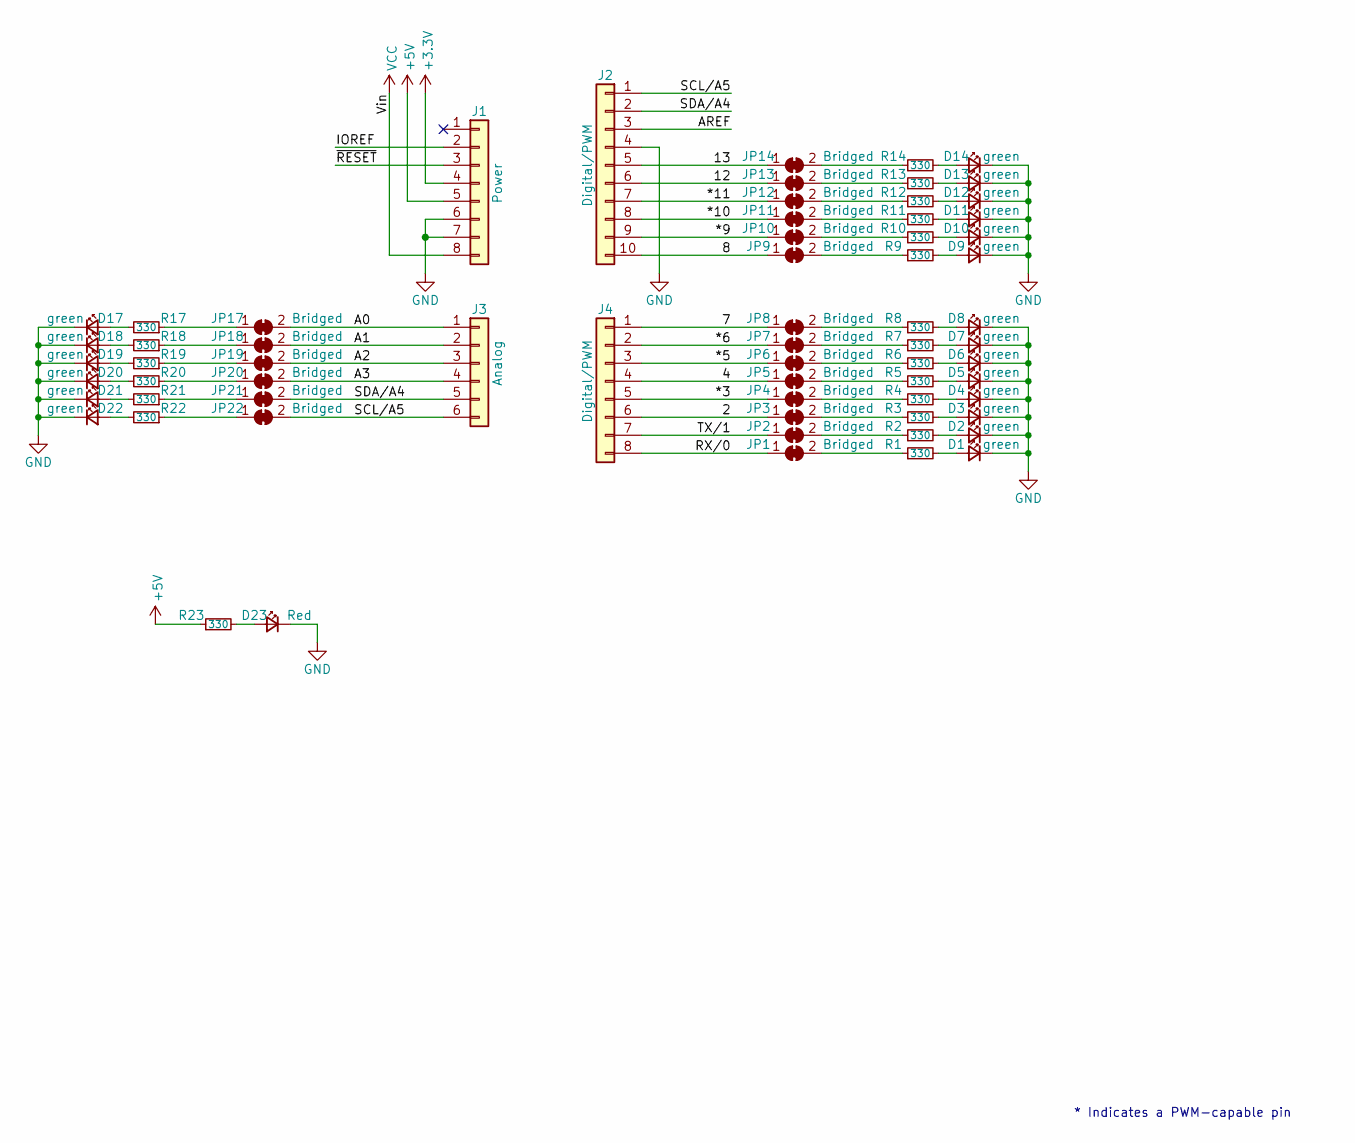
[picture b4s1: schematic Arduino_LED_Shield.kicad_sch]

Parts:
D1, D2, D3, D4, D5, D6, D7, D8, D9, D10, D11, D12, D13, D14, D17, D18, D19, D20, D21, D22: green; LED_0805_2012Metric_Pad1.15x1.40mm_HandSolder
D23: Red; LED_0805_2012Metric_Pad1.15x1.40mm_HandSolder
J1: Power; PinSocket_1x08_P2.54mm_Vertical
J2: Digital/PWM; PinSocket_1x10_P2.54mm_Vertical
J3: Analog; PinSocket_1x06_P2.54mm_Vertical
J4: Digital/PWM; PinSocket_1x08_P2.54mm_Vertical
JP1, JP2, JP3, JP4, JP5, JP6, JP7, JP8, JP9, JP10, JP11, JP12, JP13, JP14, JP17, JP18, JP19, JP20, JP21, JP22: Bridged; SolderJumper-2_P1.3mm_Bridged_Pad1.0x1.5mm
R1, R2, R3, R4, R5, R6, R7, R8, R9, R10, R11, R12, R13, R14, R17, R18, R19, R20, R21, R22, R23: 330; R_0603_1608Metric_Pad0.98x0.95mm_HandSolder

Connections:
+3V3: J1.4
+5V: J1.5, R23.1
/2: J4.6, JP3.1 (A)
/4: J4.4, JP5.1 (A)
/7: J4.1, JP8.1 (A)
/8: J2.10, JP9.1 (A)
/12: J2.6, JP13.1 (A)
/13: J2.5, JP14.1 (A)
/*3: J4.5, JP4.1 (A)
/*5: J4.3, JP6.1 (A)
/*6: J4.2, JP7.1 (A)
/*9: J2.9, JP10.1 (A)
/*10: J2.8, JP11.1 (A)
/*11: J2.7, JP12.1 (A)
/A0: J3.1, JP17.2 (B)
/A1: J3.2, JP18.2 (B)
/A2: J3.3, JP19.2 (B)
/A3: J3.4, JP20.2 (B)
/AREF: J2.3
/IOREF: J1.2
/RX/0: J4.8, JP1.1 (A)
/SCL/A5: J2.1, J3.6, JP22.2 (B)
/SDA/A4: J2.2, J3.5, JP21.2 (B)
/TX/1: J4.7, JP2.1 (A)
/~RESET: J1.3
GND: D1.1 (K), D2.1 (K), D3.1 (K), D4.1 (K), D5.1 (K), D6.1 (K), D7.1 (K), D8.1 (K), D9.1 (K), D10.1 (K), D11.1 (K), D12.1 (K), D13.1 (K), D14.1 (K), D17.1 (K), D18.1 (K), D19.1 (K), D20.1 (K), D21.1 (K), D22.1 (K), D23.1 (K), J1.6, J1.7, J2.4
unnamed: D1.2 (A), R1.2
unnamed: D2.2 (A), R2.2
unnamed: D3.2 (A), R3.2
unnamed: D4.2 (A), R4.2
unnamed: D5.2 (A), R5.2
unnamed: D6.2 (A), R6.2
unnamed: D7.2 (A), R7.2
unnamed: D8.2 (A), R8.2
unnamed: D9.2 (A), R9.2
unnamed: D10.2 (A), R10.2
unnamed: D11.2 (A), R11.2
unnamed: D12.2 (A), R12.2
unnamed: D13.2 (A), R13.2
unnamed: D14.2 (A), R14.2
unnamed: D17.2 (A), R17.2
unnamed: D18.2 (A), R18.2
unnamed: D19.2 (A), R19.2
unnamed: D20.2 (A), R20.2
unnamed: D21.2 (A), R21.2
unnamed: D22.2 (A), R22.2
unnamed: D23.2 (A), R23.2
unnamed: JP1.2 (B), R1.1
unnamed: JP2.2 (B), R2.1
unnamed: JP3.2 (B), R3.1
unnamed: JP4.2 (B), R4.1
unnamed: JP5.2 (B), R5.1
unnamed: JP6.2 (B), R6.1
unnamed: JP7.2 (B), R7.1
unnamed: JP8.2 (B), R8.1
unnamed: JP9.2 (B), R9.1
unnamed: JP10.2 (B), R10.1
unnamed: JP11.2 (B), R11.1
unnamed: JP12.2 (B), R12.1
unnamed: JP13.2 (B), R13.1
unnamed: JP14.2 (B), R14.1
unnamed: JP17.1 (A), R17.1
unnamed: JP18.1 (A), R18.1
unnamed: JP19.1 (A), R19.1
unnamed: JP20.1 (A), R20.1
unnamed: JP21.1 (A), R21.1
unnamed: JP22.1 (A), R22.1
VCC: J1.8

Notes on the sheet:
* Indicates a PWM-capable pin

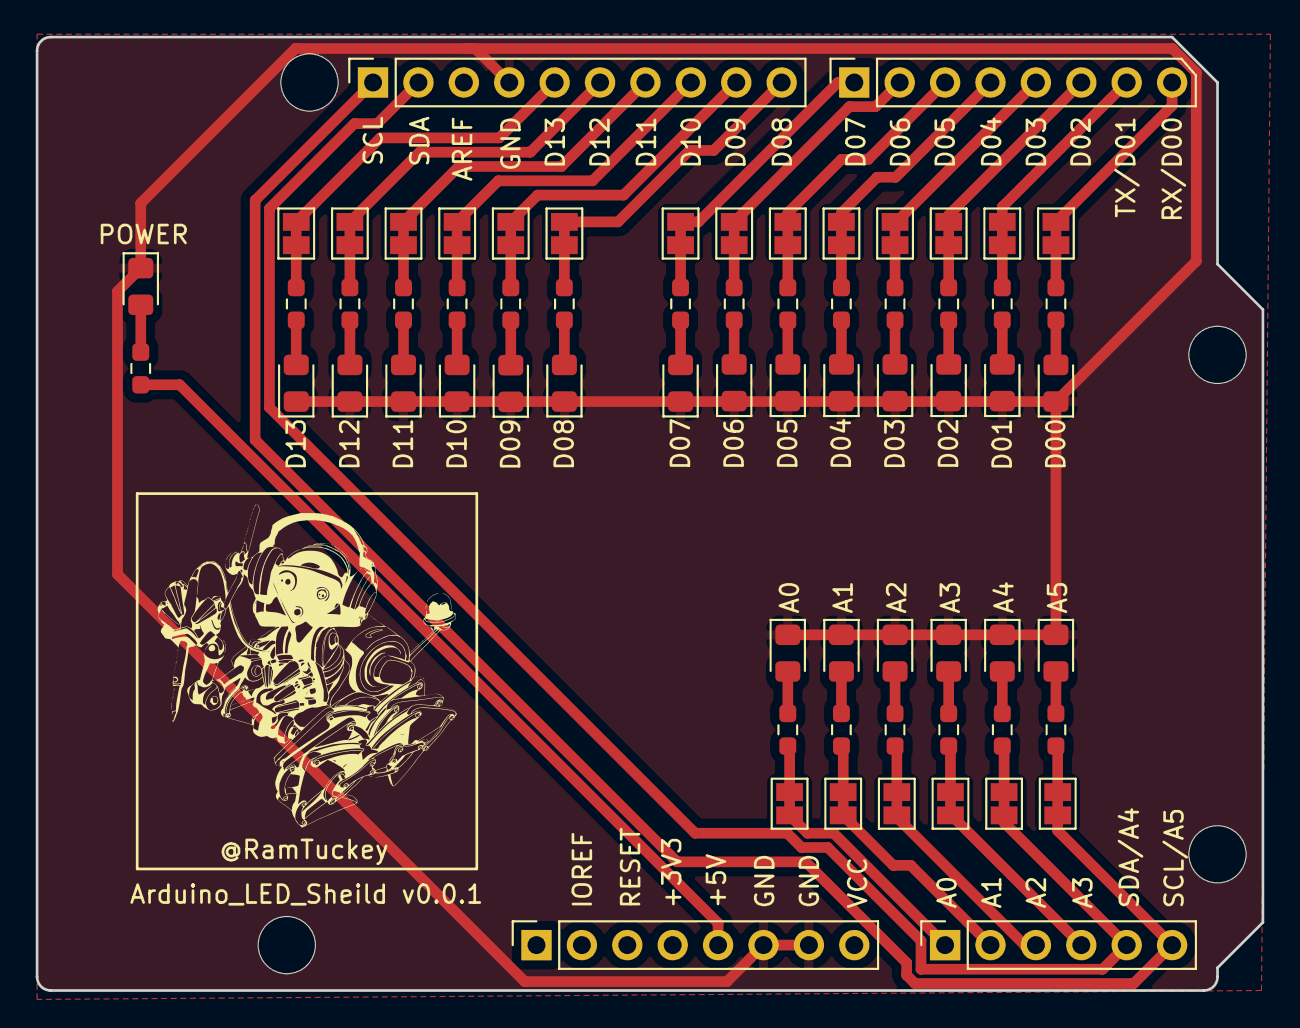
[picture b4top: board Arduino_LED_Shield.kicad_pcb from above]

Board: 2 copper layers, 68.6 x 53.3 mm, 70 parts (0 on the bottom side), 63 nets.

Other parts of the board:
MH1, MH2, MH3, MH4: MountingHole_3.2mm

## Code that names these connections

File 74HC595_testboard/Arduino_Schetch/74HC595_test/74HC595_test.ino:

// 74HC595を5個カスケード接続した場合の動作サンプル(SPI通信を使用しない場合)
const int dataPin = 2;     // SERピン
const int latchPin = 3;    // RCLKピン
const int clockPin = 4;    // SRCLKピン
void setup() {
  pinMode(dataPin, OUTPUT);
  pinMode(latchPin, OUTPUT);
  pinMode(clockPin, OUTPUT);
}


void loop() {
  wavePattern();

  doubleChasePattern();
  middleOutPattern();

  chaserPattern();
  for (int j = 0; j <= 40; j++) {
    uint64_t pattern = (j == 40) ? 0xFFFFFFFFFF : ((1ULL << j) - 1);
    updateShiftRegisters(pattern);
    delay(50);
  }
  delay(100);
  randomPattern();
  //singleChasePattern();

  //rotateChasePattern();
}

void updateShiftRegisters(uint64_t data) {
  digitalWrite(latchPin, LOW);
  for (int i = 4; i >= 0; i--) {
    shiftOut(dataPin, clockPin, MSBFIRST, (data >> (8 * i)) & 0xFF);
  }
  digitalWrite(latchPin, HIGH);
}


// 1. ウェーブ
void wavePattern() {
  for (int j = 0; j < 40; j++) {
    uint64_t pattern = 1ULL << j;
    updateShiftRegisters(pattern);
    delay(100);
  }
  delay(500);
}

// 2. 中央から放射
void middleOutPattern() {
  int middle = 20;
  for (int j = 0; j <= middle; j++) {
    uint64_t pattern = (1ULL << (middle - j)) | (1ULL << (middle + j));
    updateShiftRegisters(pattern);
    delay(100);
  }
  delay(500);
}

// 3. ランダム
void randomPattern() {
  for (int j = 0; j < 40; j++) {
    uint64_t upperBits = (uint64_t)random(0xFFFF) << 32;  // 16ビットを生成して、32ビット左にシフト
    uint64_t middleBits = (uint64_t)random(0xFFFF) << 16; // 16ビットを生成して、16ビット左にシフト
    uint64_t lowerBits = random(0xFFFF);  // 下位16ビット
    uint64_t pattern = upperBits | middleBits | lowerBits;
    updateShiftRegisters(pattern);
    delay(100);
  }
  delay(500);
}

// 4. チャーサー
void chaserPattern() {
  uint64_t pattern = 0xF;  // 初期の4つのLEDを点灯
  for (int j = 0; j < 37; j++) {
    pattern <<= 1;
    updateShiftRegisters(pattern);
    delay(100);
  }
  delay(500);
}
// 1. 単一LEDチェイス
void singleChasePattern() {
  for (int j = 0; j < 40; j++) {
    uint64_t pattern = 1ULL << j;
    updateShiftRegisters(pattern);
    delay(100);
  }
  for (int j = 38; j >= 0; j--) {
    uint64_t pattern = 1ULL << j;
    updateShiftRegisters(pattern);
    delay(100);
  }
  delay(500);
}

// 2. ダブルLEDチェイス
void doubleChasePattern() {
  for (int j = 0; j < 38; j++) {
    uint64_t pattern = (1ULL << j) | (1ULL << (j + 2));
    updateShiftRegisters(pattern);
    delay(100);
  }
  for (int j = 38; j > 0; j--) {
    uint64_t pattern = (1ULL << j) | (1ULL << (j - 2));
    updateShiftRegisters(pattern);
    delay(100);
  }
  delay(500);
}

// 3. 回転チェイス
void rotateChasePattern() {
  for (int j = 0; j < 40; j++) {
    uint64_t pattern = 1ULL << (j % 40);
    updateShiftRegisters(pattern);
    delay(100);
  }
  delay(500);
}

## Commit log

2023-09-17 add kicad
2023-12-24 push
2023-12-24 74HC595_dotmatlix2
2024-01-21 mcp23017_up
2024-03-20 Create m5glass2.ino
    uo
2024-07-15 crane_touchgfx
2026-01-18 BrightDate_WPF
2026-02-01 readme追加
2026-02-01 azure新規
2026-02-01 コード作成
2026-02-02 add grpc
